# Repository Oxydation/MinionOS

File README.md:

# MinionOS

Development of a simple OS for a BeagleBoard C4 with a ARMv7 Cortex A8-Processor (OMAP 3530). 

## The system consists of following modules and/or parts:
*  GPIO 
*  Interrupts 
*  Timers/System Timer 
*  System Calls
*  Filesystem
*  Scheduler 
*  Virtual Memory 
*  Process Management
*  Inter Process Communication
*  Basic User Apps 
*  Shell

## Drivers
### Low-Level
*  MMC_SD/SPI
*  UART 

### High-Level
*  DMX 

## Design

## Tools
* Code Composer Studio v7

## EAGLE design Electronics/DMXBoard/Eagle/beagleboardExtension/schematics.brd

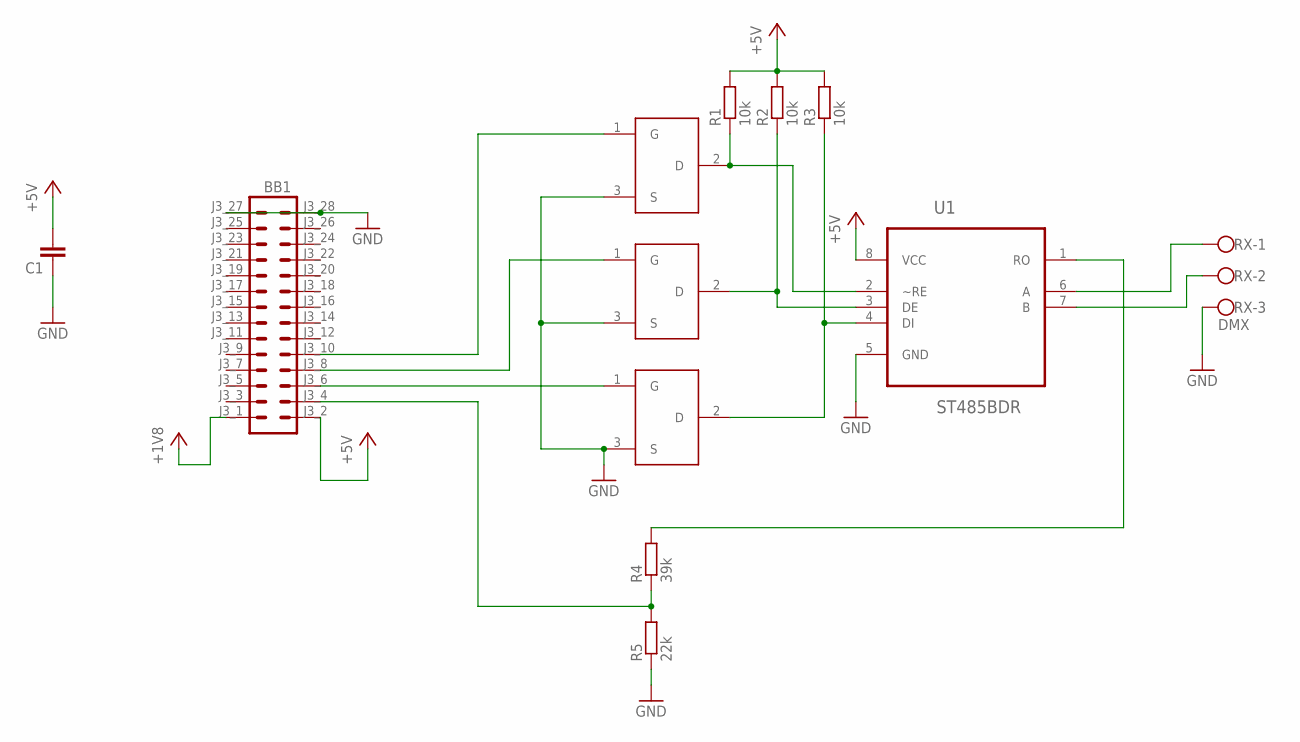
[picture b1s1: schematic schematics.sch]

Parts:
BB1: BEAGLE_EXPANSION
C1: C-EUC0603; C0603
R1, R2, R3: 10k; R0603
R4: 39k; R0603
R5: 22k; R0603
RX: DMX; W237-103
U1: ST485BDR; SOIC127P600X175-8N
U$1, U$2, U$3: SI1012CR-T1-GE3; SC75

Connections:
+3V3: BB1.J3_1 (1)
+5V: BB1.J3_2 (2), C1.2, R1.2, R2.2, R3.2, U1.8 (VCC)
GND: BB1.J3_27 (27), BB1.J3_28 (28), C1.1, R5.1, RX.3, U1.5 (GND), U$1.3 (S), U$2.3 (S), U$3.3 (S)
unnamed: R1.1, U1.2 (~RE), U$1.2 (D)
unnamed: R2.1, U1.3 (DE), U$3.2 (D)
unnamed: BB1.J3_4 (4), R4.1, R5.2
unnamed: R3.1, U1.4 (DI), U$2.2 (D)
unnamed: BB1.J3_6 (6), U$2.1 (G)
unnamed: BB1.J3_8 (8), U$3.1 (G)
unnamed: BB1.J3_10 (10), U$1.1 (G)
unnamed: R4.2, U1.1 (RO)
unnamed: RX.1, U1.6 (A)
unnamed: RX.2, U1.7 (B)

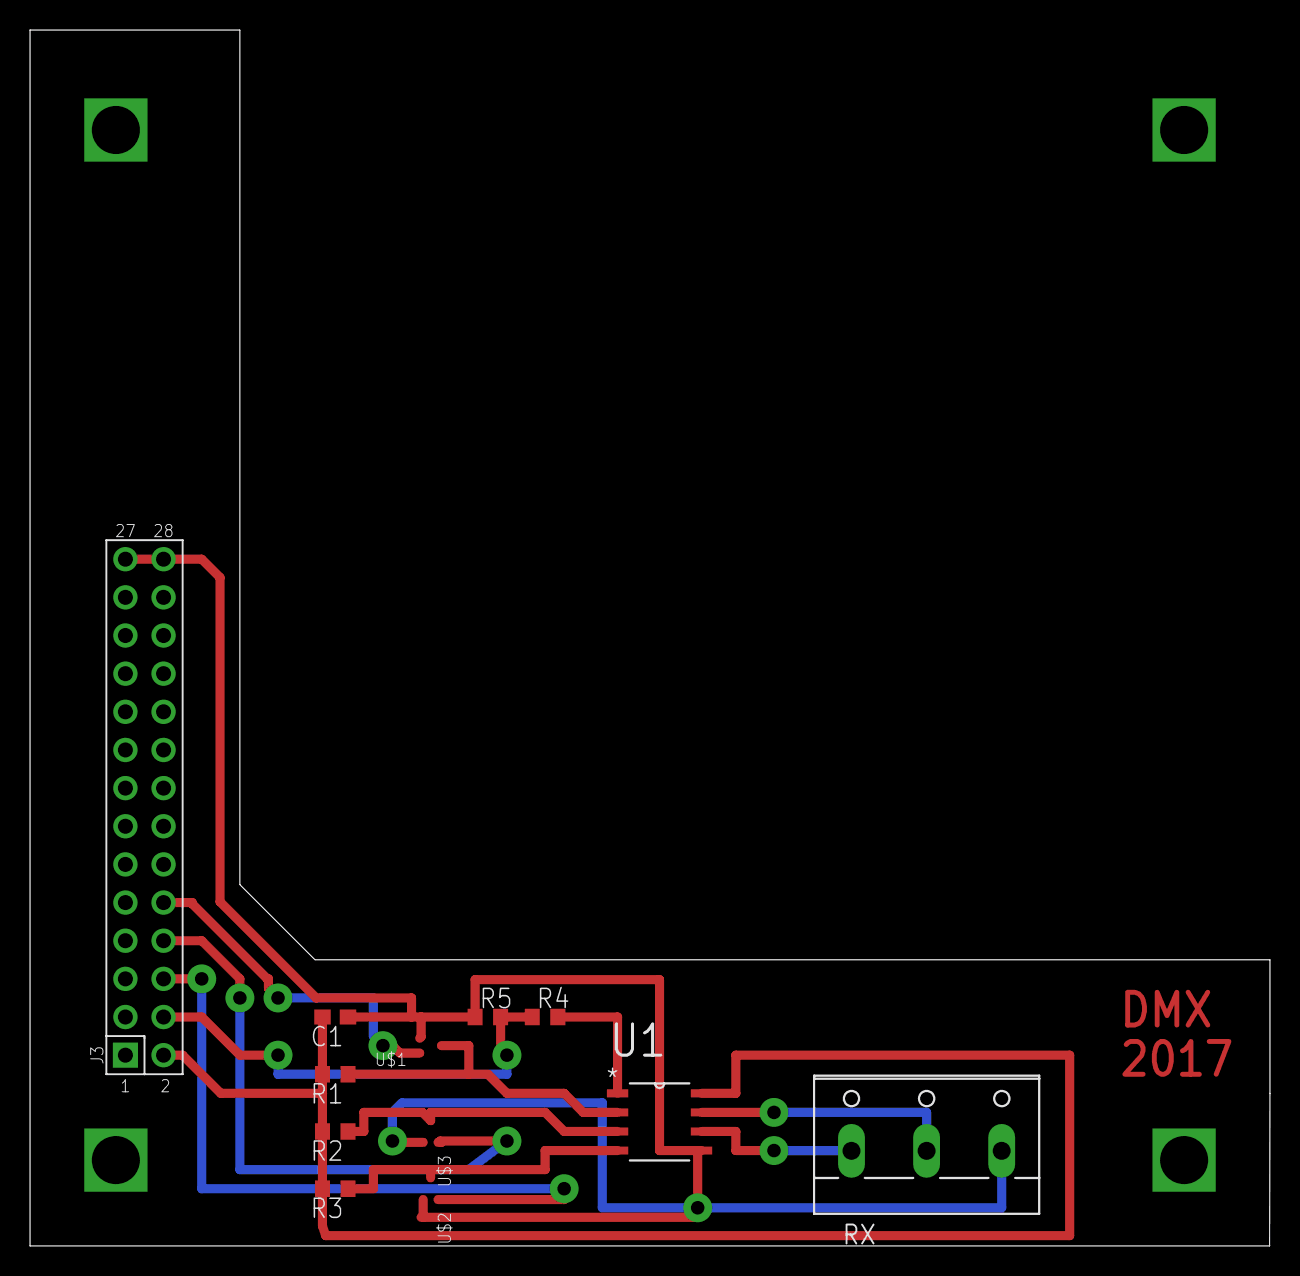
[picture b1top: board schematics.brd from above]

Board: 2 copper layers, 82.5 x 81.0 mm, 12 parts (0 on the bottom side), 12 nets.

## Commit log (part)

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2017-03-15 Added example project (LED blink)
2017-03-15 Added new project (prepared for timer); with improvements from arduino (bitClear,bitSet, writeDigital, readDigital, pinMode, ...) Additional header files for the timer
2017-03-18 Added a lot of definitions for timer and interrupts Startet implementation of basic interrupt handler
2017-03-18 Some adjustments and implementations Interrupts not finished/working yet
2017-03-19 Added some IRQ vectors as definitions and finished register and handling interrupt functions
2017-03-20 Bug fixing stuff, but setting the INTCPS_MIR_CLEAR does not work (app hangs)
2017-03-20 Timer is working but interrupt not yet
2017-03-20 Added some pdfs and books (Important books: TRM (spruf98y.pdf) and ARM architecture reference manual (armv7-a-r-manual.pdf))
2017-03-22 Added some useful books Improved interrupt, added asm to map interrupt vectors
2017-03-28 Some improvements
2017-03-28 First success with interrupt: when calling "_call_swi" i get a reset interrupt Timer interrupt still not working
2017-03-29 Some modifications to test interrupts
2017-04-02 Moved OS to DRAM0 Added stacks for various modes (irq, svc & abt) Added new book: ARM assembly language tools users guide
2017-04-02 Fixed timer, set clock to 32 kHz LED blinks now every ~2s Improved boot.asm and removed unecessary stuff
2017-04-02 Fixed timer, now working Blinking with ~1s
2017-04-02 Added comments Removed unnecessary stuff
2017-04-05 Init main OS project Adjusted gitignore Added FIQ stack
2017-04-05 Adjusted architecture of the OS, added folders and moved files
2017-04-05 Renamed devices specific modules
2017-04-05 Added empty files for folders
2017-04-05 syscalls
2017-04-05 Led Syscall
2017-04-05 Implemented a abstract timer module, which allows setting the interval and behaviour
2017-04-05 Trying to get two leds independent to work
2017-04-05 Two timers are running independent now
2017-04-05 Removed unused code
2017-04-06 Added small code convention and some pdfs
2017-04-06 Updated style conventions
2017-04-06 Updated schema
2017-04-06 Made kernel timer more abstract from omap registers
2017-04-09 Renaming functions to convention style: moduleName_functionName()
2017-04-09 Renamed file name of modules
2017-04-10 defined user-stack, set user-stack for user-mode, added function for context switch from privileged mode to user mode
2017-04-12 Changed module name, included DS_Store in gitignore
2017-04-12 changed includes
2017-04-12 Fixed naming Removed empty lines Moved static declarations into class file Removed extern modifiers
2017-04-12 Added context switch asm
2017-04-13 Started with implementation of scheduler Added latest c4 reference for beagleboard Added new feature, to enable/disable system timer subscription Added two processes with custom memory Fixed context 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
2017-04-17 Implemented scheduler and processmanager Able to load a process (static, via function) Only one process is runnable at the moment Reserved memory for processes via linker Added generic queue.c Implem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
2017-04-17 Scheduler is now able to exit process and start another Problem still: cannot retrieve corrent context to restore later
2017-04-19 syscalls/clean up
2017-04-19 restore main
2017-04-19 led abstraction
2017-04-19 rename fuction enableLed
2017-04-19 pragma without SWI Number
2017-04-19 rename SysCalls
2017-05-09 Added mmu.h file with declarations of needed functions and structs
2017-05-11 Pagetables are initialised with fault entries
2017-05-11 Removed printf Changed R13 to SP (increased readability) Forwarding latest process pcb to interrupt handler Cleanded up PCB struct Added basic process manager Loading processes before interrupts.c Si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
2017-05-15 Page tables can now be filled with valid entries
2017-05-17 Fixed scheduler and context switch Context switch now only in isr Adjusted variable names to def. style
2017-05-17 base address of L1 master page table is set in MMU and entries for L2 page tables are made in L1 master page table
2017-05-17 Added DMX board schematics and layout Adjusted readme file
2017-05-17 Fix error
2017-05-17 uart init
2017-05-18 Basic read/write
2017-05-20 Added working driver for SD card (read func. only)
2017-05-20 Adapt code to style guidelines
2017-05-20 Allow address to read from as parameter
2017-05-21 Remove empty lines at the beginning of functions
2017-05-21 Remove unneeded variables + magic numbers
2017-05-22 domain access can be assigned
2017-05-22 the mmu can be enabled
2017-05-24 Compile error fix
2017-05-24 init dmx
2017-05-24 Add config options
2017-05-24 tests..
2017-05-25 enable/disable module
2017-05-25 First success with blinking and moving head
2017-05-26 Improved dmx module Fixed timer
2017-05-29 mmu can be enabled and direct memory mapping is working (refactoring still necessary)
2017-05-30 uart cleanup
    * Replaced local bit manipulation operations with
    global/bitManipulation.h
    * static for module local stuff, uart prefix for public stuff
    * Moved uart defines to kernel/devices/omap3530/includes/uart.h
2017-05-31 Made some small improvements New function to reset timer counter
2017-05-31 vfs/device drivers init
2017-05-31 include uart + basic shell
2017-06-01 SystemCalls module refactor
2017-06-01 Implemented VFS syscalls and moved shell to user space
2017-06-02 readdir wip
2017-06-05 processes with virtual addresses (which are different from the physical ones) can be loaded
2017-06-05 refactoring of process loading
2017-06-05 added PageStatus_t type for reserved/free pages
2017-06-05 refactoring of function to write PT-entry in master page table
2017-06-06 page table for new process is created dynamically
2017-06-06 added Process_t struct for saving the page table with its process, implemented function for process switch in MMU (not yet in use)
2017-06-07 readdir proto
2017-06-07 Further improvements and changes to dmx Adjustments to get a useful signal - but still not working Added function to update uart setting without complete init Added delay function
2017-06-07 Initial working commit for filesystem
2017-06-07 refactoring of function for initializing process in mmu
2017-06-07 implemented assembler functions for getting data fault status, data fault address, instruction fault status and instruction fault address registers
2017-06-07 First working version of DMX :)
2017-06-07 Added a dmx driver for the TMH7 devices Refactoring
2017-06-07 extract io module, extract shell utilities
2017-06-07 Added file descriptors
2017-06-07 implemented functions for allocating free pages, refactoring of initialisation of process
2017-06-07 added check if page in physical memory is still free before initialising the process
2017-06-08 Added driver settings for dmx: MH-X25
2017-06-09 gitignore update
2017-06-10 Further improvements and adjustments to control two or more dmx devices
2017-06-11 more fs integration
2017-06-13 Return correct number of bytes read
2017-06-13 Resume last position when reading bytes from file
2017-06-14 require all paths to start with '/'
2017-06-14 Check if first char is slash when opening file
2017-06-14 Add null checks
2017-06-14 Fixed dmx
2017-06-14 process can be killed if it isn't the current process running
2017-06-14 Reverted main to previous version
2017-06-14 Added function to list dir entries
2017-06-14 First trials to read data from sd card and build up question system
2017-06-14 process kill is working with more than 2 processes
2017-06-14 refractoring process kill in scheduler
2017-06-14 refactoring
2017-06-14 Filter out filenames which start with fwd slash
2017-06-14 Fix bug when reading dir entries across multiple sectors
2017-06-14 Reduce SD card command delay
2017-06-15 refactored mmu code
2017-06-15 modified gitignore
2017-06-16 process manager is responsible for process kill, not mmu
2017-06-16 changed includes in scheduler.h
2017-06-16 process manager is responsible for initializing process, not mmu
2017-06-16 process manager calculates stack pointer dynamically
2017-06-16 Improved reading from sd card and fixed bugs
2017-06-19 fixing .gitignore
2017-06-19 file from sd card can be opened
2017-06-19 fixed .gitignore
2017-06-19 remove temporary pseudo filesystem
2017-06-19 add check for path (start and end with slash)
2017-06-20 file can be loaded from sd-card (but there is still an error in fileSystem_readFile(...) that the wrong number of read bytes is given back when reading the last few bytes of the file
2017-06-20 process can be loaded from the sd-card and started
2017-06-21 Fix return read bytes bug
2017-06-21 fix ls for root dir
2017-06-21 Process is removed from scheduler after it has finished
2017-06-21 added idle process to scheduler
2017-06-21 added nullpointer and used it for terminating a process
2017-06-21 ipc and ipc device driver prototype
2017-06-21 process can be loaded from sd card with only one read buffer
2017-06-21 commented error from vfs merge out
2017-06-22 Made various improvements to the dmx 123 game
2017-06-22 Added third moving head
2017-06-22 Added serial tts project
2017-06-22 heap size set to 0x20000
2017-06-22 added hex to int parser
2017-06-22 added intel hex parser
2017-06-22 loader can parse intel hex files
2017-06-22 fixed bug in util.asm (pc was not set after function call)
2017-06-23 Reading COM port from console various improvements
2017-06-23 removed systemCallApi from main project (moved to library)
2017-06-23 ipc, semaphores & blocked processes
2017-06-23 added application LEDON with memory mapping for use in virtual memory
2017-06-23 Fixed serialtts tool (to read all) Added icon
2017-06-23 Added v1.0 of serialtts tool
2017-06-23 game123 finalization
2017-06-24 added code for loading elf-file (still problem with reading section name)
2017-06-25 Fix cluster reading bug
2017-06-25 little fix in elfParser
2017-06-25 Fixed serial tts application Removed unused folders Cleaned up main
2017-06-25 Printing answer as text instead of just the number
2017-06-25 process can be loaded from sd-card and started
2017-06-25 added projects for turning second led on and off, mapped .cinit and .const sections as well
2017-06-25 Added control dmx syscall
2017-06-25 replace SWI dispatch if chain with switch
2017-06-25 initialize sd card during sdCardFs init
2017-06-25 moved semaphore to scheduler module
2017-06-26 use vfs directly in loader instead of using syscalls
2017-06-26 semaphore syscalls
2017-06-26 semaphore tests
2017-06-26 changed access permissions for memory regions
2017-06-26 changed domains for memory regions
2017-06-26 Added get bit range Added interrupt functionality to uart module Fixed interrupt bit (32 instead of 8 bits)
2017-06-26 Read type of interrupt
2017-06-26 game123 project init
2017-06-27 moved minionIO to systemCalls lib and added timeout to uart receive
2017-06-27 Fixed project (libs)
2017-06-27 refactoring elfParser
2017-06-27 Remove delay when reading buffer
2017-06-27 added syscall to load program/start process
2017-06-27 fixed bug when loading elf file
2017-06-27 added shell command "start"
2017-06-27 switched LOW/HIGH logic to account for buggy digitalWrite
2017-06-27 initialize sdCard together with sdCardFs (and consequently with vfs_init)
2017-06-27 extracted all commands to their own file and added Command_t abstraction
2017-06-27 cleanup main removed unused includes removed uartInit (automatically done in vfs_init) removed sdCard_init (automatically done in vfs_init) removed LED DIR (automatically done in led hal) removed LED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
2017-06-27 Working version with mmu, but no scheduler NOT FINAL
2017-06-27 Also working with two leds WoopWoop
2017-06-27 Removed applications (not used anymore) Disabled leds to use app
2017-06-28 added dmx include in main and correct getNextDir for subdirs
2017-07-05 Neue Gerätetreiber: GPIO & DMX DMX und LED sysCalls entfernt und mit Fileoperationen ersetzt Shell: 'cat' in 'read' umbenannt und 'write hinzugefügt'
